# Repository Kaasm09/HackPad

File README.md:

# HackPad
My hackpad features 4 programmable keys, a rotary encoder with a push switch, and a few fun decorations!

# Features
* 4 keys
* 1 rotary encoder
* Bottom mounted case providing a softer, more comftorable typing experience

# Cad Model
The only external parts for assembling the case required are 8 M3 screws!

# Schematic

# PCB

# BOM
Heres everything you need to assemble!
* 1x XIAO RP2040
* 4x Cherry MX Switches
* 1x EC11 Rotary Encoder
* 1x Case (3 Parts)
* 1x Knob
* 8x M3 16mm Screws

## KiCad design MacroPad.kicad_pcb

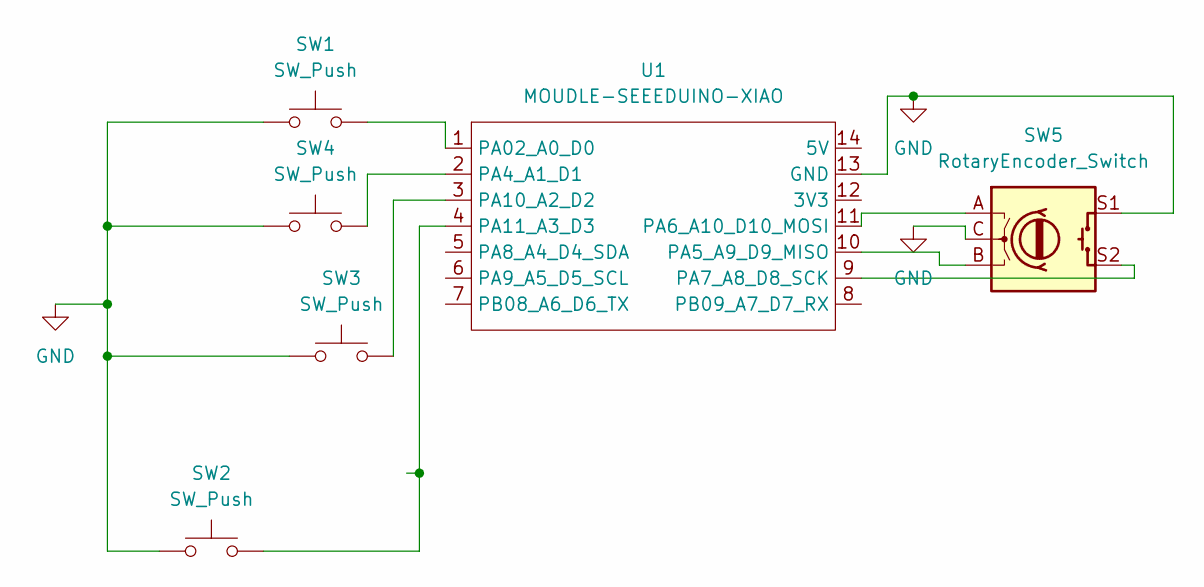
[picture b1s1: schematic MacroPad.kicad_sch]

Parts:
SW1, SW2, SW3, SW4: SW_Push; SW_Cherry_MX_1.00u_PCB
SW5: RotaryEncoder_Switch; RotaryEncoder_Alps_EC11E-Switch_Vertical_H20mm
U1: MOUDLE-SEEEDUINO-XIAO; XIAO-RP2040-SMD

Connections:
GND: SW1.1, SW2.1, SW3.1, SW4.1, SW5.C, SW5.S1, U1.13 (GND)
unnamed: SW1.2, U1.1 (PA02_A0_D0)
unnamed: SW4.2, U1.2 (PA4_A1_D1)
unnamed: SW5.B, U1.10 (PA5_A9_D9_MISO)
unnamed: SW5.A, U1.11 (PA6_A10_D10_MOSI)
unnamed: SW5.S2, U1.9 (PA7_A8_D8_SCK)
unnamed: SW3.2, U1.3 (PA10_A2_D2)
unnamed: SW2.2, U1.4 (PA11_A3_D3)

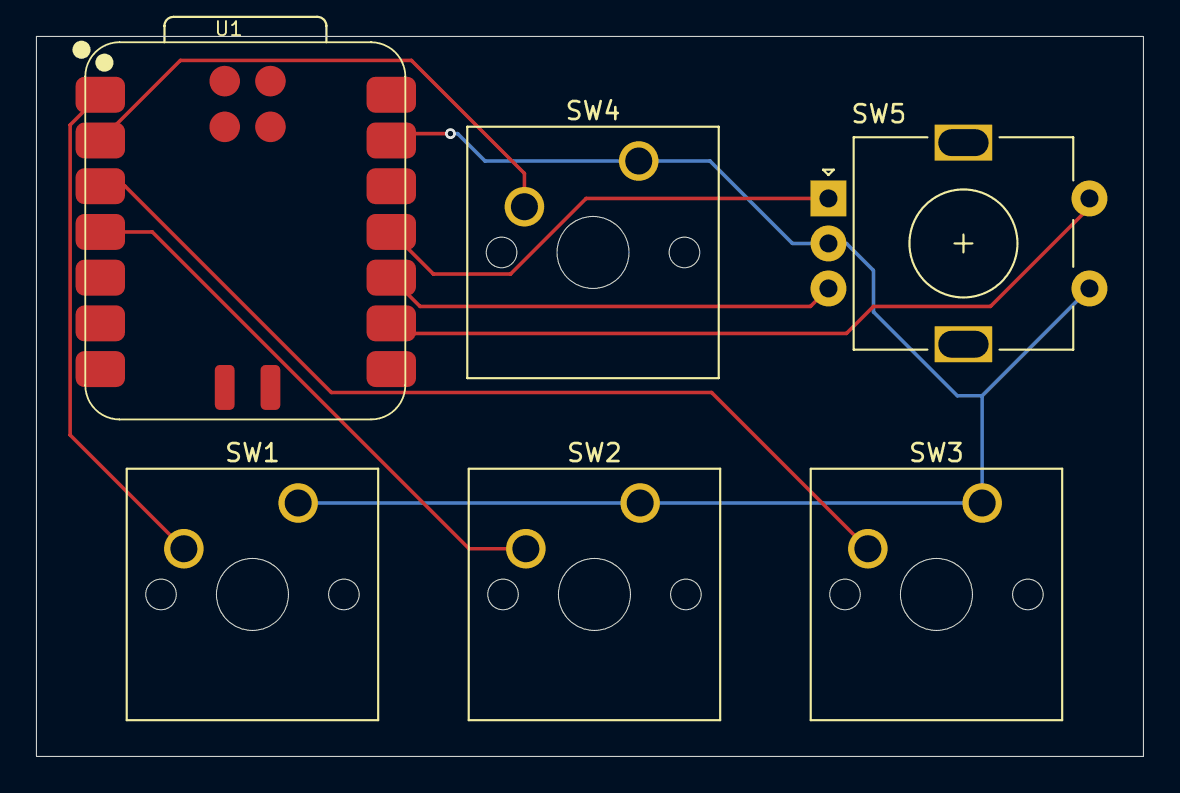
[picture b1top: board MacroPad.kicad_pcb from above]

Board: 2 copper layers, 61.5 x 40.0 mm, 6 parts (0 on the bottom side), 8 nets.

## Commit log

2026-03-01 Finished adding relevant files
2026-03-01 Forgot knob lol
